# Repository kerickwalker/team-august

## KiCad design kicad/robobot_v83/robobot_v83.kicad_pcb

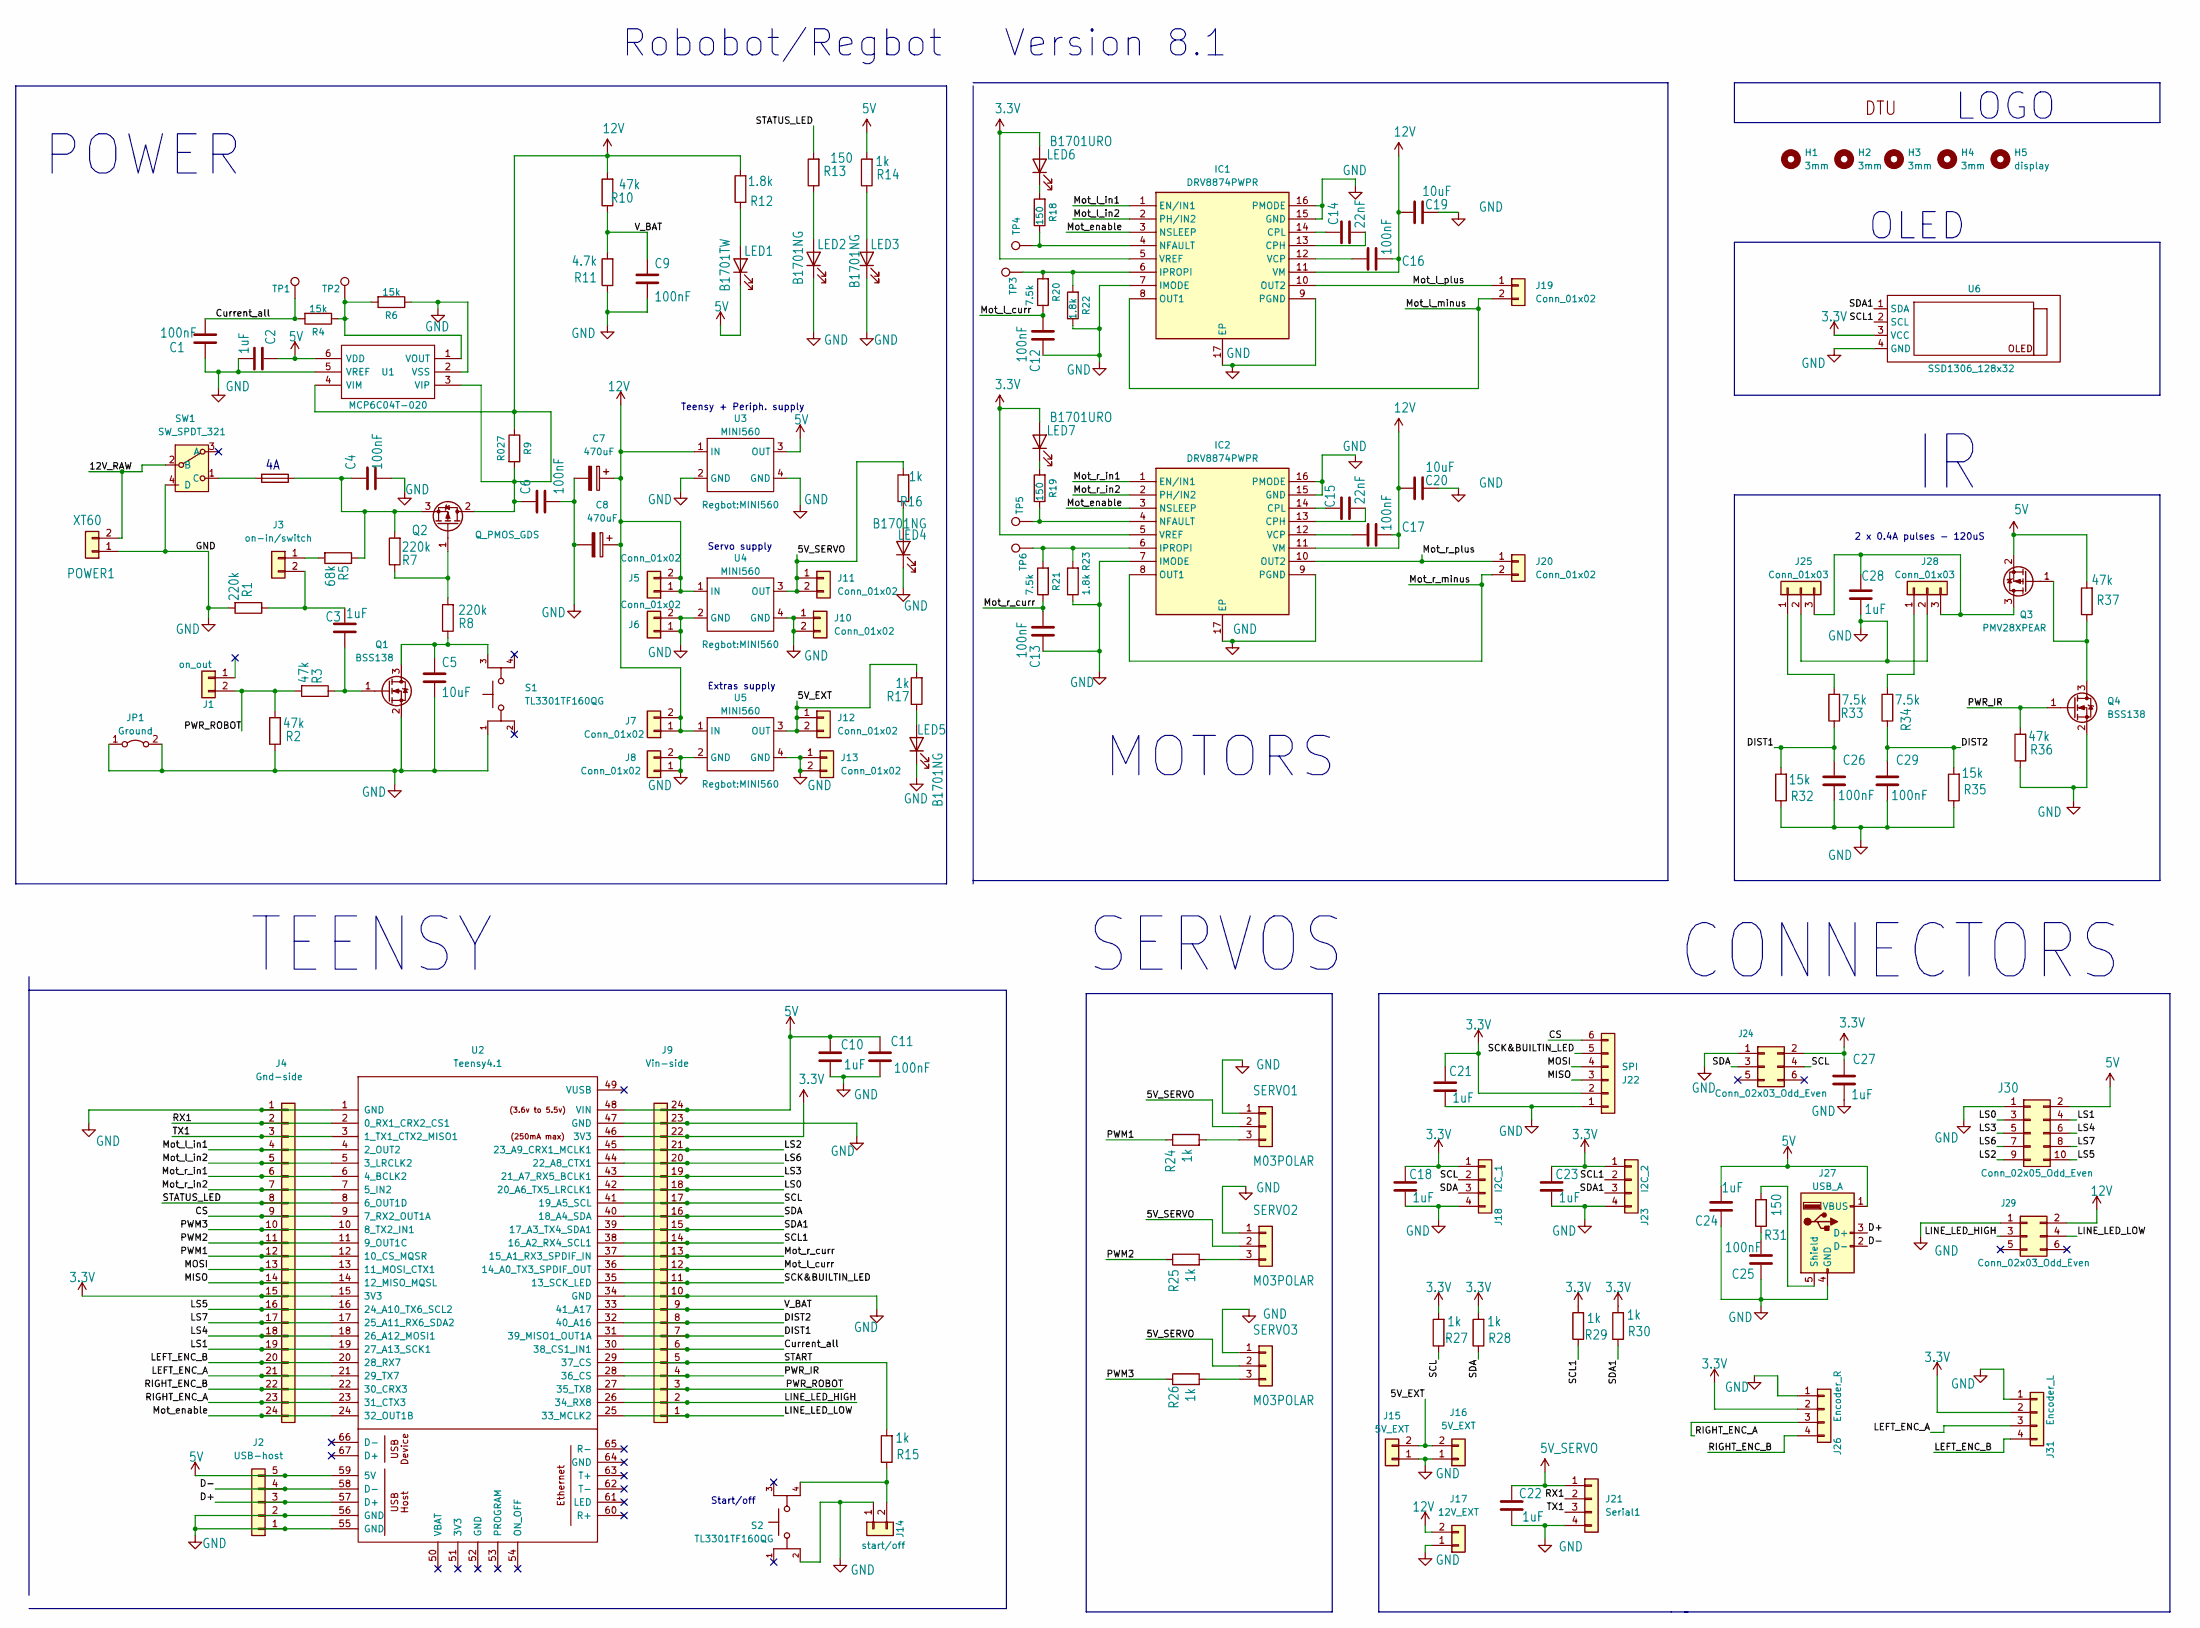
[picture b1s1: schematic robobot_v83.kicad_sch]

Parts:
C1, C4, C6, C9, C11, C12, C13, C16, C17, C25, C26, C29: 100nF; C_0805_2012Metric
C2, C3, C10, C18, C21, C22, C23, C24, C27, C28: 1uF; C_0805_2012Metric
C5, C19, C20: 10uF; C_0805_2012Metric
C7, C8: 470uF; C_Radial_D10.0mm_H16.0mm_P5.00mm
C14, C15: 22nF; C_0805_2012Metric
FUSE1: 4A; Fuseholder_Littelfuse_Nano2_154x
H1, H2, H3, H4: 3mm; MountingHole_3.2mm_M3; Mfg Part # not mounted
H5: display; MountingHole_3.2mm_M3; Mfg Part # not mounted
IC1, IC2: DRV8874PWPR; SOP65P640X120-17N; Mouser Part Number 595-DRV8874PWPR
J1: on_out; JST_PH_B2B-PH-K_1x02_P2.00mm_Vertical
J2: USB-host; PinSocket_1x05_P2.54mm_Vertical
J3: on-in/switch; JST_PH_B2B-PH-K_1x02_P2.00mm_Vertical
J4: Gnd-side; PinSocket_1x24_P2.54mm_Vertical; Mfg Part # not mounted
J5, J7: Conn_01x02; PinSocket_1x02_P2.54mm_Vertical
J6, J8, J10, J11, J12, J13: Conn_01x02; PinHeader_1x02_P2.54mm_Vertical
J9: Vin-side; PinSocket_1x24_P2.54mm_Vertical; Mfg Part # not mounted
J14: start/off; JST_PH_B2B-PH-K_1x02_P2.00mm_Vertical
J15, J16: 5V_EXT; JST_PH_B2B-PH-K_1x02_P2.00mm_Vertical
J17: 12V_EXT; JST_PH_B2B-PH-K_1x02_P2.00mm_Vertical
J18: I2C_1; JST_PH_B4B-PH-K_1x04_P2.00mm_Vertical
J19, J20: Conn_01x02; Molex_KK-254_AE-6410-02A_1x02_P2.54mm_Vertical
J21: Serial1; JST_PH_B4B-PH-K_1x04_P2.00mm_Vertical
J22: SPI; JST_PH_B6B-PH-K_1x06_P2.00mm_Vertical; Mfg Part # not mounted
J23: I2C_2; JST_PH_B4B-PH-K_1x04_P2.00mm_Vertical
J24, J29: Conn_02x03_Odd_Even; IDC-Header_2x03_P2.54mm_Vertical
J25, J28: Conn_01x03; JST_PH_B3B-PH-K_1x03_P2.00mm_Vertical
J26: Encoder_R; JST_PH_B4B-PH-K_1x04_P2.00mm_Vertical
J27: USB_A; USB_A_ASSMANN_A-TOP_VERTICAL
J30: Conn_02x05_Odd_Even; IDC-Header_2x05_P2.54mm_Vertical
J31: Encoder_L; JST_PH_B4B-PH-K_1x04_P2.00mm_Vertical
JP1: Ground; PinHeader_1x02_P2.54mm_Vertical
LED1: B1701TW; LED_0805_2012Metric
LED2, LED3, LED4, LED5: B1701NG; LED_0805_2012Metric
LED6, LED7: B1701URO; LED_0805_2012Metric
POWER1: XT60
Q1, Q4: BSS138; SOT-23
Q2: Q_PMOS_GDS; D-PAK_TO252AA
Q3: PMV28XPEAR; SOT-23
R1, R7, R8: 220k; R_0805_2012Metric
R2, R3, R10, R36, R37: 47k; R_0805_2012Metric
R4, R6, R32, R35: 15k; R_0805_2012Metric
R5: 68k; R_0805_2012Metric
R9: R027; R_1206_3216Metric
R11: 4.7k; R_0805_2012Metric
R12, R22, R23: 1.8k; R_0805_2012Metric
R13, R18, R19, R31: 150; R_0805_2012Metric
R14, R15, R16, R17, R24, R25, R26, R27, R28, R29, R30: 1k; R_0805_2012Metric
R20, R21, R33, R34: 7.5k; R_0805_2012Metric
S1, S2: TL3301TF160QG; TL3301; PARTREV E
SERVO1, SERVO2, SERVO3: M03POLAR; MOLEX-1X3
SW1: SW_SPDT_321; RS-PRO-1MS1T2B3M7QES; Mfg Part # not mounted
TP1, TP2, TP3, TP4, TP5, TP6: sup.cur.; TestPoint_Pad_D1.5mm
U1: MCP6C04T-020; SOT95P280X145-6N; Manufacturer_Part_Number MCP6C04T-020E/CHY; Mouser Part Number 579-MCP6C04T020ECHY
U2: Teensy4.1; Teensy41
U3, U4, U5: MINI560
U6: SSD1306_128x32; PinSocket_1x04_P2.54mm_Vertical
U$1: DTUMEDIUM-9MM; DTU-MEDIUM-9MM

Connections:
+3.3V: C18.1, C21.1, C23.1, C27.1, IC1.5 (VREF), IC2.5 (VREF), J4.15, J9.22, J18.1, J22.2, J23.1, J24.2, J26.2, J31.2, LED6.2 (A), LED7.2 (A), R27.2, R28.2, R29.2, R30.2, U2.15 (3V3), U2.46 (3V3), U6.3 (VCC)
+12V: C6.1, C7.1, C8.1, C16.2, C17.2, C19.1, C20.1, IC1.11 (VM), IC2.11 (VM), J5.1, J5.2, J7.1, J7.2, J17.2, J29.2, Q2.2 (D), R9.1, R9.2, R10.2, R12.2, U1.3 (VIP), U1.4 (VIM), U3.1 (IN), U4.1 (IN), U5.1 (IN)
/5V_EXT: J12.1, J12.2, J15.2, J16.2, R17.2, U5.3 (OUT)
/5V_SERVO: J11.1, J11.2, R16.2, SERVO1.2, SERVO2.2, SERVO3.2, U4.3 (OUT)
/12V_RAW: POWER1.2, SW1.2 (B)
/CS: J4.9, J22.6, U2.9 (7_RX2_OUT1A)
/Current_all: C1.2, J9.6, R4.2, TP1.1, U2.30 (38_CS1_IN1)
/D+: J2.3, J27.3 (D+), U2.57 (D+)
/D-: J2.4, J27.2 (D-), U2.58 (D-)
/DIST1: C26.1, J9.7, R32.2, R33.1, U2.31 (39_MISO1_OUT1A)
/DIST2: C29.1, J9.8, R34.1, R35.2, U2.32 (40_A16)
/LEFT_ENC_A: J4.21, J31.3, U2.21 (29_TX7)
/LEFT_ENC_B: J4.20, J31.4, U2.20 (28_RX7)
/LINE_LED_HIGH: J9.2, J29.3, U2.26 (34_RX8)
/LINE_LED_LOW: J9.1, J29.4, U2.25 (33_MCLK2)
/LS0: J9.18, J30.3, U2.42 (20_A6_TX5_LRCLK1)
/LS1: J4.19, J30.4, U2.19 (27_A13_SCK1)
/LS2: J9.21, J30.9, U2.45 (23_A9_CRX1_MCLK1)
/LS3: J9.19, J30.5, U2.43 (21_A7_RX5_BCLK1)
/LS4: J4.18, J30.6, U2.18 (26_A12_MOSI1)
/LS5: J4.16, J30.10, U2.16 (24_A10_TX6_SCL2)
/LS6: J9.20, J30.7, U2.44 (22_A8_CTX1)
/LS7: J4.17, J30.8, U2.17 (25_A11_RX6_SDA2)
/MISO: J4.14, J22.3, U2.14 (12_MISO_MQSL)
/MOSI: J4.13, J22.4, U2.13 (11_MOSI_CTX1)
/Mot_enable: IC1.3 (NSLEEP), IC2.3 (NSLEEP), J4.24, U2.24 (32_OUT1B)
/Mot_l_curr: C12.2, J9.12, R20.1, U2.36 (14_A0_TX3_SPDIF_OUT)
/Mot_l_in1: IC1.1 (EN/IN1), J4.4, U2.4 (2_OUT2)
/Mot_l_in2: IC1.2 (PH/IN2), J4.5, U2.5 (3_LRCLK2)
/Mot_l_minus: IC1.8 (OUT1), J19.2
/Mot_l_plus: IC1.10 (OUT2), J19.1
/Mot_r_curr: C13.2, J9.13, R21.1, U2.37 (15_A1_RX3_SPDIF_IN)
/Mot_r_in1: IC2.1 (EN/IN1), J4.6, U2.6 (4_BCLK2)
/Mot_r_in2: IC2.2 (PH/IN2), J4.7, U2.7 (5_IN2)
/Mot_r_minus: IC2.8 (OUT1), J20.2
/Mot_r_plus: IC2.10 (OUT2), J20.1
/PWM1: J4.12, R24.1, U2.12 (10_CS_MQSR)
/PWM2: J4.11, R25.1, U2.11 (9_OUT1C)
/PWM3: J4.10, R26.1, U2.10 (8_TX2_IN1)
/PWR_IR: J9.4, Q4.1 (G), R36.2, U2.28 (36_CS)
/PWR_ROBOT: J1.2, J9.3, R2.2, R3.2, U2.27 (35_TX8)
/RIGHT_ENC_A: J4.23, J26.3, U2.23 (31_CTX3)
/RIGHT_ENC_B: J4.22, J26.4, U2.22 (30_CRX3)
/RX1: J4.2, J21.2, U2.2 (0_RX1_CRX2_CS1)
/SCK&BUILTIN_LED: J9.11, J22.5, U2.35 (13_SCK_LED)
/SCL: J9.17, J18.2, J24.4, R27.1, U2.41 (19_A5_SCL)
/SCL1: J9.14, J23.2, R29.1, U2.38 (16_A2_RX4_SCL1), U6.2 (SCL)
/SDA: J9.16, J18.3, J24.3, R28.1, U2.40 (18_A4_SDA)
/SDA1: J9.15, J23.3, R30.1, U2.39 (17_A3_TX4_SDA1), U6.1 (SDA)
/START: J9.5, R15.2, U2.29 (37_CS)
/STATUS_LED: J4.8, R13.2, U2.8 (6_OUT1D)
/TX1: J4.3, J21.3, U2.3 (1_TX1_CTX2_MISO1)
/V_BAT: C9.1, J9.9, R10.1, R11.2, U2.33 (41_A17)
GND: C1.1, C2.2, C4.2, C5.2, C6.2, C7.2, C8.2, C9.2, C10.2, C11.2, C12.1, C13.1, C18.2, C19.2, C20.2, C21.2, C22.2, C23.2, C24.2, C25.2, C26.2, C27.2, C28.2, C29.2, IC1.7 (IMODE), IC1.9 (PGND), IC1.15 (GND), IC1.16 (PMODE), IC1.17 (EP), IC2.7 (IMODE), IC2.9 (PGND), IC2.15 (GND), IC2.16 (PMODE), IC2.17 (EP), J2.1, J2.2, J4.1, J6.1, J6.2, J8.1, J8.2, J9.10, J9.23, J10.1, J10.2, J13.1, J13.2, J14.1, J15.1, J16.1, J17.1, J18.4, J21.4, J22.1, J23.4, J24.1, J25.2, J26.1, J27.4 (GND), J28.2, J29.1, J30.1, J31.1, JP1.1 (A), JP1.2 (B), LED2.1 (K), LED3.1 (K), LED4.1 (K), LED5.1 (K), POWER1.1, Q1.2 (S), Q4.2 (S), R1.2, R2.1, R6.1, R11.1, R22.1, R23.1, R32.1, R35.1, R36.1, S1.1, S2.2, SERVO1.1, SERVO2.1, SERVO3.1, SW1.4 (D), U1.2 (VSS), U1.5 (VREF), U2.1 (GND), U2.34 (GND), U2.47 (GND), U2.55 (GND), U2.56 (GND), U3.2 (GND), U3.4 (GND), U4.2 (GND), U4.4 (GND), U5.2 (GND), U5.4 (GND), U6.4 (GND)
unnamed: C25.1, R31.1
unnamed: C14.2, IC1.13 (CPH)
unnamed: C14.1, IC1.14 (CPL)
unnamed: IC1.6 (IPROPI), R20.2, R22.2, TP3.1
unnamed: IC1.4 (NFAULT), R18.1, TP4.1
unnamed: C16.1, IC1.12 (VCP)
unnamed: C15.2, IC2.13 (CPH)
unnamed: C15.1, IC2.14 (CPL)
unnamed: IC2.6 (IPROPI), R21.2, R23.2, TP6.1
unnamed: IC2.4 (NFAULT), R19.1, TP5.1
unnamed: C17.1, IC2.12 (VCP)
unnamed: J3.1, R5.2
unnamed: C3.2, J3.2, R1.1
unnamed: J14.2, R15.1, S2.4
unnamed: J25.1, R33.2
unnamed: C28.1, J25.3, J28.3, Q3.3 (D)
unnamed: J27.5 (Shield), R31.2
unnamed: J28.1, R34.2
unnamed: LED1.2 (A), R12.1
unnamed: LED2.2 (A), R13.1
unnamed: LED3.2 (A), R14.1
unnamed: LED4.2 (A), R16.1
unnamed: LED5.2 (A), R17.1
unnamed: LED6.1 (K), R18.2
unnamed: LED7.1 (K), R19.2
unnamed: C5.1, Q1.3 (D), R8.1, S1.3
unnamed: C3.1, Q1.1 (G), R3.1
unnamed: Q2.1 (G), R7.1, R8.2
unnamed: C4.1, FUSE1.1, Q2.3 (S), R5.1, R7.2
unnamed: Q3.1 (G), Q4.3 (D), R37.1
unnamed: R24.2, SERVO1.3
unnamed: R25.2, SERVO2.3
unnamed: R26.2, SERVO3.3
unnamed: FUSE1.2, SW1.1 (C)
unnamed: R4.1, R6.2, TP2.1, U1.1 (VOUT)

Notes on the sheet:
Teensy + Periph. supply
TEENSY
2 x 0.4A pulses - 120uS
Start/off
Servo supply
MOTORS
Version 8.1
POWER
SERVOS
Robobot/Regbot
OLED
LOGO
CONNECTORS
Extras supply

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
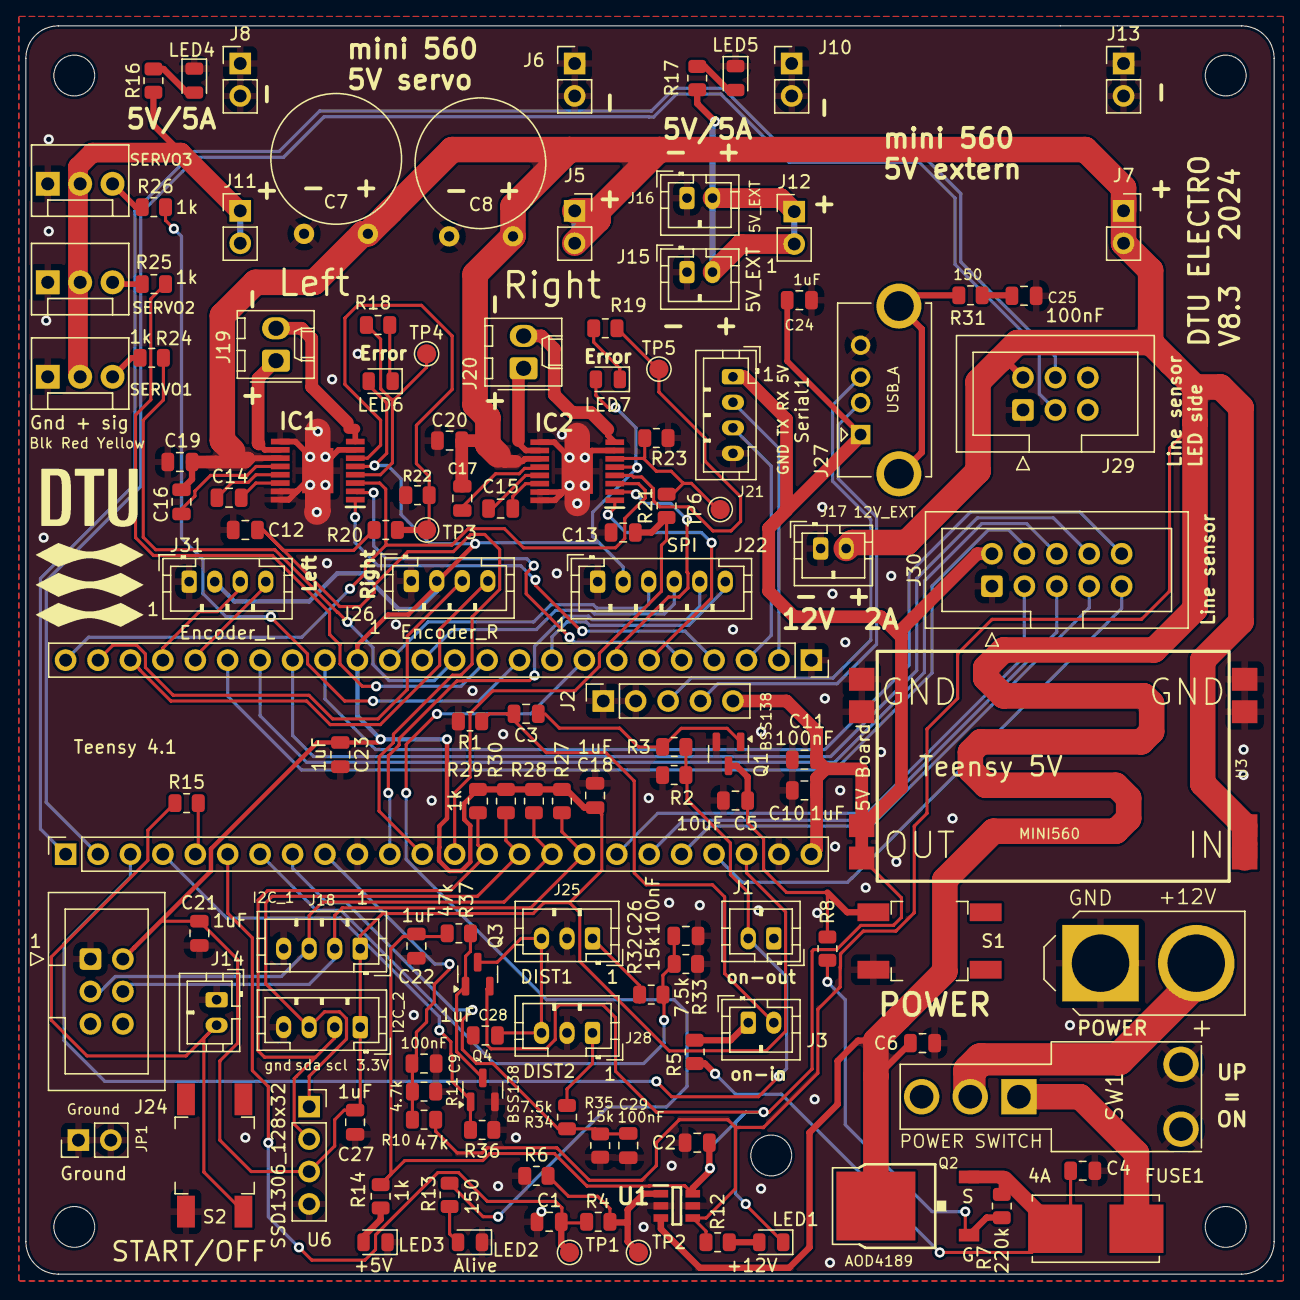
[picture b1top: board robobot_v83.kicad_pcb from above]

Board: 2 copper layers, 97.8 x 97.8 mm, 134 parts (1 on the bottom side), 90 nets.

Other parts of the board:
U$1#2: DTUMEDIUM-9MM; DTU-MEDIUM-9MM

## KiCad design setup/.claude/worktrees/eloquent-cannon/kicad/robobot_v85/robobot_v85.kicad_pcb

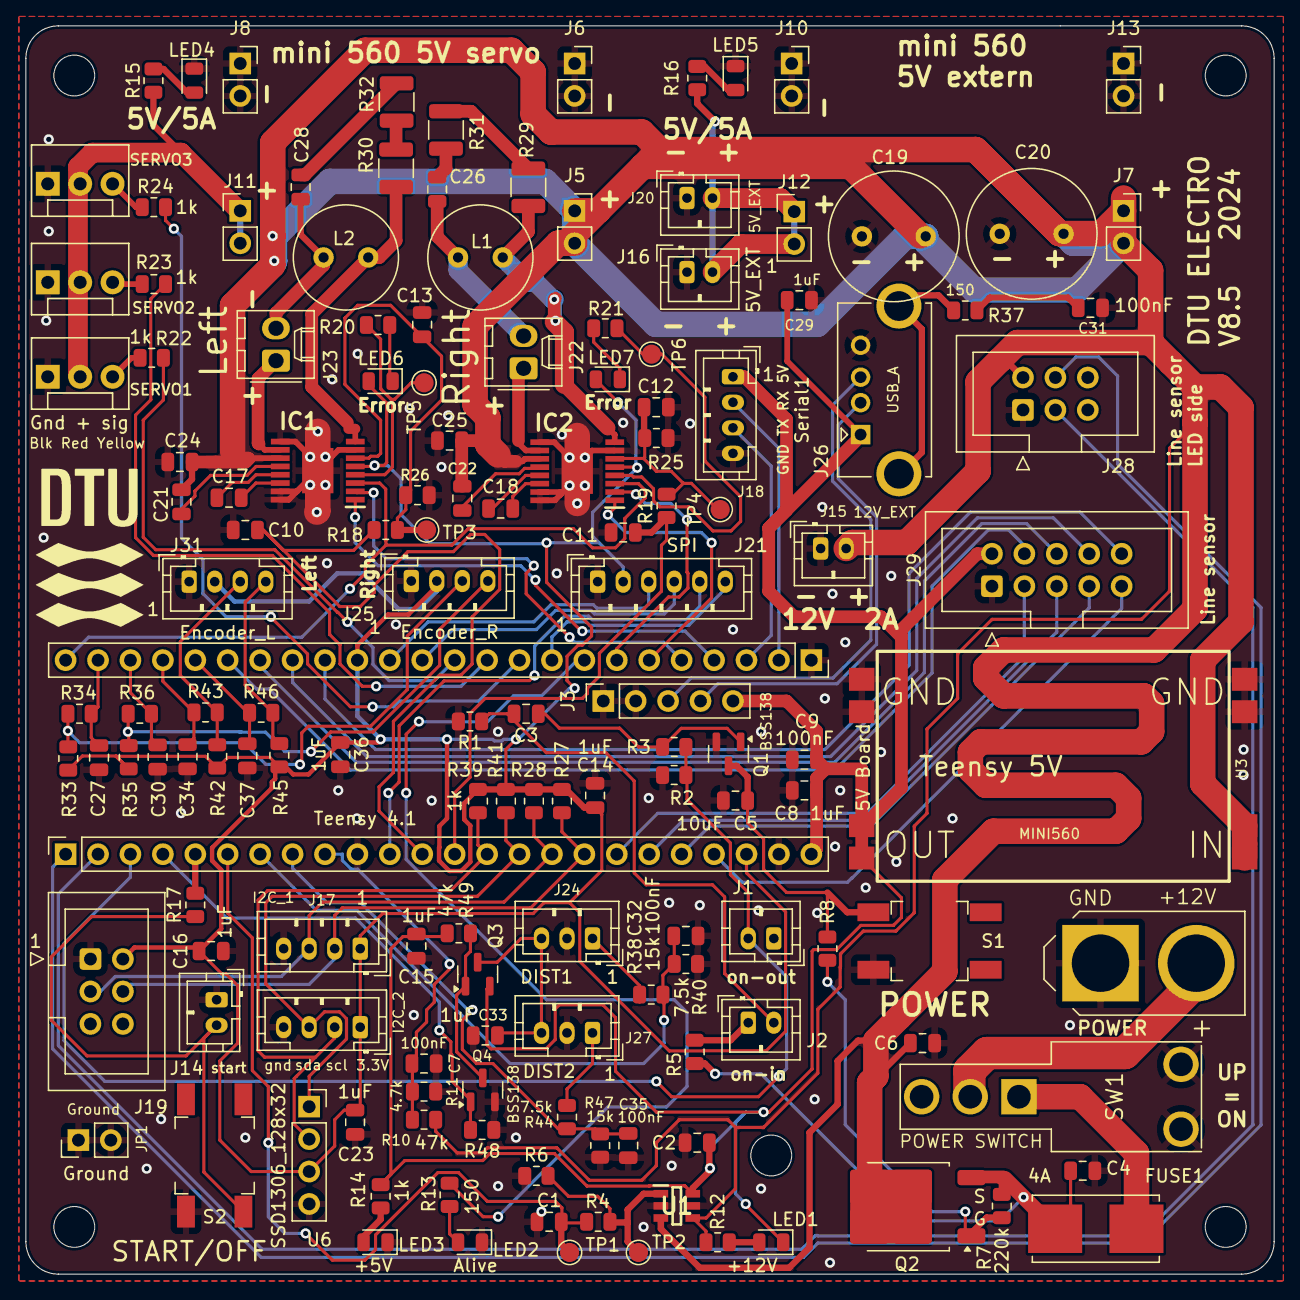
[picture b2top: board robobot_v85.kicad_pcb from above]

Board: 2 copper layers, 97.8 x 97.8 mm, 156 parts (1 on the bottom side), 100 nets.

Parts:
C1, C4, C6, C7, C9, C12, C13, C21, C22, C26, C28, C31, C32, C35: 100nF; C_0805_2012Metric
C2, C3, C8, C14, C15, C16, C23, C29, C33, C36: 1uF; C_0805_2012Metric
C5, C24, C25: 10uF; C_0805_2012Metric
C10, C11, C17, C18: 22nF; C_0805_2012Metric
C19, C20: 470uF; C_Radial_D10.0mm_H16.0mm_P5.00mm
C27, C30, C34, C37: 2.2nF; C_0805_2012Metric
FUSE1: 4A; Fuseholder_Littelfuse_Nano2_154x
H1, H2, H3, H4: 3mm; MountingHole_3.2mm_M3
H5: display; MountingHole_3.2mm_M3
IC1, IC2: DRV8874PWPR; SOP65P640X120-17N
J1: on_out; JST_PH_B2B-PH-K_1x02_P2.00mm_Vertical
J2: on-in/switch; JST_PH_B2B-PH-K_1x02_P2.00mm_Vertical
J3: USB-host; PinSocket_1x05_P2.54mm_Vertical
J4: Gnd-side; PinSocket_1x24_P2.54mm_Vertical
J5, J6, J7, J8, J10, J13: Conn_01x02; PinSocket_1x02_P2.54mm_Vertical
J9: Vin-side; PinSocket_1x24_P2.54mm_Vertical
J11, J12: Conn_01x02; PinHeader_1x02_P2.54mm_Vertical
J14: start/off; JST_PH_B2B-PH-K_1x02_P2.00mm_Vertical
J15: 12V_EXT; JST_PH_B2B-PH-K_1x02_P2.00mm_Vertical
J16, J20: 5V_EXT; JST_PH_B2B-PH-K_1x02_P2.00mm_Vertical
J17: I2C_1; JST_PH_B4B-PH-K_1x04_P2.00mm_Vertical
J18: Serial1; JST_PH_B4B-PH-K_1x04_P2.00mm_Vertical
J19, J28: Conn_02x03_Odd_Even; IDC-Header_2x03_P2.54mm_Vertical
J21: SPI; JST_PH_B6B-PH-K_1x06_P2.00mm_Vertical
J22, J23: Conn_01x02; Molex_KK-254_AE-6410-02A_1x02_P2.54mm_Vertical
J24, J27: Conn_01x03; JST_PH_B3B-PH-K_1x03_P2.00mm_Vertical
J25: Encoder_R; JST_PH_B4B-PH-K_1x04_P2.00mm_Vertical
J26: USB_A; USB_A_ASSMANN_A-TOP_VERTICAL
J29: Conn_02x05_Odd_Even; IDC-Header_2x05_P2.54mm_Vertical
J30: I2C_2; JST_PH_B4B-PH-K_1x04_P2.00mm_Vertical
J31: Encoder_L; JST_PH_B4B-PH-K_1x04_P2.00mm_Vertical
JP1: Ground; PinHeader_1x02_P2.54mm_Vertical
L1, L2: 20uH; C_Radial_D8.0mm_H11.5mm_P3.50mm
LED1: B1701TW; LED_0805_2012Metric
LED2, LED3, LED4, LED5: B1701NG; LED_0805_2012Metric
LED6, LED7: B1701URO; LED_0805_2012Metric
POWER1: XT60
Q1, Q4: BSS138; SOT-23
Q2: Q_PMOS_GDS; TO-252-2
Q3: PMV28XPEAR; SOT-23
R1, R7, R8: 220k; R_0805_2012Metric
R2, R3, R10, R48, R49: 47k; R_0805_2012Metric
R4, R6, R38, R47: 15k; R_0805_2012Metric
R5: 68k; R_0805_2012Metric
R11: 4.7k; R_0805_2012Metric
R12, R25, R26: 1.8k; R_0805_2012Metric
R13, R20, R21, R37: 150; R_0805_2012Metric
R14, R15, R16, R17, R22, R23, R24, R27, R28, R34, R36, R39, R41, R43, R46: 1k; R_0805_2012Metric
R18, R19, R33, R35, R40, R42, R44, R45: 7.5k; R_0805_2012Metric
R29, R30, R31, R32: 56R; R_1210_3225Metric
S1, S2: TL3301TF160QG; TL3301
SERVO1, SERVO2, SERVO3: M03POLAR; MOLEX-1X3
SW1: SW_SPDT_321; RS-PRO-1MS1T2B3M7QES
TP1, TP2, TP3, TP4, TP5, TP6: sup.cur.; TestPoint_Pad_D1.5mm
U1: MCP6C04T-020; SOT95P280X145-6N
U3: MINI560
U6: SSD1306_128x32; PinSocket_1x04_P2.54mm_Vertical
U$1, U$1#2: DTUMEDIUM-9MM; DTU-MEDIUM-9MM

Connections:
+3.3V: C14.1, C16.1, C23.1, C36.1, IC1.5 (VREF), IC2.5 (VREF), J4.15, J9.22, J17.1, J19.2, J21.2, J25.2, J30.1, J31.2, LED6.2 (A), LED7.2 (A), R27.2, R28.2, R33.2, R35.2, R39.2, R41.2, R42.2, R45.2, U6.3 (VCC)
+5V: C2.1, C8.1, C9.1, C15.1, C29.1, J3.5, J9.24, J18.1, J26.1 (VBUS), J29.2, LED1.1 (K), Q3.2 (S), R14.2, R49.2, U1.6 (VDD), U3.3 (OUT)
+12V: C6.1, C19.1, C20.1, C21.2, C22.2, C24.1, C25.1, IC1.11 (VM), IC2.11 (VM), J5.1, J5.2, J7.1, J7.2, J15.2, J28.2, Q2.2 (D), R10.2, R12.2, U1.3 (VIP), U1.4 (VIM), U3.1 (IN)
/5V_EXT: J12.1, J12.2, J16.2, J20.2, R16.2
/5V_SERVO: J11.1, J11.2, R15.2, SERVO1.2, SERVO2.2, SERVO3.2
/12V_RAW: POWER1.2, SW1.2 (B)
/CS: J4.9, J21.6
/Current_all: C1.2, J9.6, R4.2, TP1.1
/D+: J3.3, J26.3 (D+)
/D-: J3.4, J26.2 (D-)
/DIST1: C32.1, J9.7, R38.2, R40.1
/DIST2: C35.1, J9.8, R44.1, R47.2
/LEFT_ENC_A: C34.1, J4.21, R43.1
/LEFT_ENC_B: C37.1, J4.20, R46.1
/LINE_LED_HIGH: J9.2, J28.3
/LINE_LED_LOW: J9.1, J28.4
/LS0: J9.18, J29.3
/LS1: J4.19, J29.4
/LS2: J9.21, J29.9
/LS3: J9.19, J29.5
/LS4: J4.18, J29.6
/LS5: J4.16, J29.10
/LS6: J9.20, J29.7
/LS7: J4.17, J29.8
/MISO: J4.14, J21.3
/MOSI: J4.13, J21.4
/Mot_enable: IC1.3 (NSLEEP), IC2.3 (NSLEEP), J4.24
/Mot_l_curr: C10.2, J9.12, R18.1
/Mot_l_in1: IC1.1 (EN/IN1), J4.4
/Mot_l_in2: IC1.2 (PH/IN2), J4.5
/Mot_l_minus: C28.2, J23.2, L2.2
/Mot_l_plus: IC1.10 (OUT2), J23.1
/Mot_r_curr: C11.2, J9.13, R19.1
/Mot_r_in1: IC2.1 (EN/IN1), J4.6
/Mot_r_in2: IC2.2 (PH/IN2), J4.7
/Mot_r_minus: C26.2, J22.2, L1.2
/Mot_r_plus: IC2.10 (OUT2), J22.1
/PWM1: J4.12, R22.1
/PWM2: J4.11, R23.1
/PWM3: J4.10, R24.1
/PWR_IR: J9.4, Q4.1 (G), R48.2
/PWR_ROBOT: J1.2, J9.3, R2.2, R3.2
/RIGHT_ENC_A: C27.1, J4.23, R34.1
/RIGHT_ENC_B: C30.1, J4.22, R36.1
/RX1: J4.2, J18.2
/SCK&BUILTIN_LED: J9.11, J21.5
/SCL: J9.17, J17.2, J19.4, R27.1
/SCL1: J9.14, J30.2, R39.1, U6.2 (SCL)
/SDA: J9.16, J17.3, J19.3, R28.1
/SDA1: J9.15, J30.3, R41.1, U6.1 (SDA)
/START: J9.5, R17.2
/STATUS_LED: J4.8, R13.2
/TX1: J4.3, J18.3
/V_BAT: C7.1, J9.9, R10.1, R11.2
GND: C1.1, C2.2, C4.2, C5.2, C6.2, C7.2, C8.2, C9.2, C10.1, C11.1, C12.1, C13.1, C14.2, C15.2, C16.2, C19.2, C20.2, C23.2, C24.2, C25.2, C27.2, C29.2, C30.2, C31.2, C32.2, C33.2, C34.2, C35.2, C36.2, C37.2, IC1.7 (IMODE), IC1.9 (PGND), IC1.15 (GND), IC1.16 (PMODE), IC1.17 (EP), IC2.7 (IMODE), IC2.9 (PGND), IC2.15 (GND), IC2.16 (PMODE), IC2.17 (EP), J3.1, J3.2, J4.1, J6.1, J6.2, J8.1, J8.2, J9.10, J9.23, J10.1, J10.2, J13.1, J13.2, J14.1, J15.1, J16.1, J17.4, J18.4, J19.1, J20.1, J21.1, J24.2, J25.1, J26.4 (GND), J27.2, J28.1, J29.1, J30.4, J31.1, JP1.1 (A), JP1.2 (B), LED2.1 (K), LED3.1 (K), LED4.1 (K), LED5.1 (K), POWER1.1, Q1.2 (S), Q4.2 (S), R1.2, R2.1, R6.1, R11.1, R25.1, R26.1, R38.1, R47.1, R48.1, S1.1, S2.2, SERVO1.1, SERVO2.1, SERVO3.1, SW1.4 (D), U1.2 (VSS), U1.5 (VREF), U3.2 (GND), U3.4 (GND), U6.4 (GND)
unnamed: C26.1, R31.1
unnamed: C28.1, R32.1
unnamed: C31.1, R37.1
unnamed: C17.2, IC1.13 (CPH)
unnamed: C17.1, IC1.14 (CPL)
unnamed: C13.2, IC1.6 (IPROPI), R18.2, R26.2, TP3.1
unnamed: IC1.4 (NFAULT), R20.1, TP5.1
unnamed: IC1.8 (OUT1), L2.1, R30.2
unnamed: C21.1, IC1.12 (VCP)
unnamed: C18.2, IC2.13 (CPH)
unnamed: C18.1, IC2.14 (CPL)
unnamed: C12.2, IC2.6 (IPROPI), R19.2, R25.2, TP4.1
unnamed: IC2.4 (NFAULT), R21.1, TP6.1
unnamed: IC2.8 (OUT1), L1.1, R29.2
unnamed: C22.1, IC2.12 (VCP)
unnamed: J2.1, R5.2
unnamed: C3.2, J2.2, R1.1
unnamed: J14.2, R17.1, S2.4
unnamed: J24.1, R40.2
unnamed: C33.1, J24.3, J27.3, Q3.3 (D)
unnamed: J25.3, R33.1, R34.2
unnamed: J25.4, R35.1, R36.2
unnamed: J26.5 (Shield), R37.2
unnamed: J27.1, R44.2
unnamed: J31.3, R42.1, R43.2
unnamed: J31.4, R45.1, R46.2
unnamed: LED1.2 (A), R12.1
unnamed: LED2.2 (A), R13.1
unnamed: LED3.2 (A), R14.1
unnamed: LED4.2 (A), R15.1
unnamed: LED5.2 (A), R16.1
unnamed: LED6.1 (K), R20.2
unnamed: LED7.1 (K), R21.2
unnamed: C5.1, Q1.3 (D), R8.1, S1.3
unnamed: C3.1, Q1.1 (G), R3.1
unnamed: Q2.1 (G), R7.1, R8.2
unnamed: C4.1, FUSE1.1, Q2.3 (S), R5.1, R7.2
unnamed: Q3.1 (G), Q4.3 (D), R49.1
unnamed: R29.1, R31.2
unnamed: R30.1, R32.2
unnamed: R22.2, SERVO1.3
unnamed: R23.2, SERVO2.3
unnamed: R24.2, SERVO3.3
unnamed: FUSE1.2, SW1.1 (C)
unnamed: R4.1, R6.2, TP2.1, U1.1 (VOUT)

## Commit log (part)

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2026-03-02 add python script for teleop control
2026-03-02 calibrate hsv values
2026-03-06 remove accidentally added copyright
2026-03-06 code cleanup
2026-03-08 Kalman filter implementation in separate files.
2026-03-08 fix in the model related to pitch
2026-03-08 Multi sensor implementation of Kalman filter.
2026-03-08 updated folder strucutre and made changes accordingly
2026-03-08 Sensor conversion has been created that will map raw sensor to states
2026-03-08 Final implementation using the raw sensor input for the Kalman filter with the converter.
2026-03-09 camera calibration scripts and params
2026-03-09 Add perception module: line detection, ground projection, and ArUco detection
2026-03-11 Clean baseline: full source snapshot
2026-03-11 Robot current state: teensy-dev starting point
2026-03-11 full system re-verification after git revert, all fixes confirmed working
2026-03-12 Track build outputs and sync all changes: add build artifacts, update logs, and code changes for line following, calibration, and debug.
2026-03-12 Add notes bundle, rolling line calibration, --test flag, and master-lost stop
2026-03-12 reverted mqtt-client and sedge changes
2026-03-13 implemented PID, sedge: tuning block at top, with print options
2026-03-13 line-follow: recovery turn toward lastLineSide, recovery_timeout_s in sedge, doc in notes
2026-03-13 update on params
2026-03-13 Kalman real-time application for the robot.
2026-03-13 kalman is back
2026-03-13 added a ball catching test function
2026-03-13 added functionality to control the robot and servo manually
2026-03-15 Line follow: crossing-count state machine, leave delay, hard turns at 3+/5+, 4th stop+turn+1.3m, driveTurn/driveDistance, single-line print (crossingCnt, left/rightMost), green/red GPIO, sedge sensor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
2026-03-16 Added more sensors that will be needed.
2026-03-18 Backing up today to save before Friday.
2026-03-18 Kalman filter implementation for teleoperation control
2026-03-18 Internal Kalman class added for fallback
2026-03-18 Added is.quiet under uservice.py
2026-03-18 same
2026-03-18 bug fix 4818923589
2026-03-18 patch
2026-03-18 pushback
2026-03-19 green button, red button and teensy_interfac is handled properly, no master mismatches and no zombie mqtt processes
2026-03-19 standardize teensy_interface process, implement roundabout-test
2026-03-19 rebuilt ip_disp, roundabout tests
2026-03-20 add ball detection functionality with configurable parameters and GUI controls
2026-03-27 Resolve merge conflict in uservice.py, keep upstream version
2026-04-07 initial pure pursuit controller
2026-04-07 ingore CLAUDE.md
2026-04-07 add mqtt_python/CLAUDE.md to .gitignore
2026-04-07 restored notes
2026-04-07 remove unused get-pose.py script and update related documentation
2026-04-07 add debug mode to mqtt_client_path_follow.py for Kalman pose verification
2026-04-07 changed readme
2026-04-10 added roundabout test
2026-04-10 Enhance quiet mode functionality in UService: include debug flag and improve message handling
2026-04-10 refactor: field map, localization, and visualization modules
2026-04-10 Add velocity and turnrate tracking to path-following service
2026-04-10 Refactor code structure for improved readability and maintainability
2026-04-10 Negate trajectory y and heading in drivePathFollow for consistent frame of reference
2026-04-10 Add velocity parameter to compute_command for enhanced control in Pure Pursuit
2026-04-10 Update LOOKAHEAD_DIST and MAX_TURNRATE for improved trajectory tracking
2026-04-10 Refactor SKalman to capture yaw offsets at reset for improved measurement accuracy; update trajectory data and increase LOOKAHEAD_DIST for better tracking.
2026-04-10 Update .gitignore and change log for Pure Pursuit coordinate convention and silent mode enhancements
2026-04-11 Enhance teleoperation script with countdown before start and improve output clarity
2026-04-11 Add interpolate_waypoints.py for cubic-spline resampling of teleop waypoints
2026-04-11 Update path_following.md to document trajectory authoring workflow and clarify waypoint capture process
2026-04-11 Refactor cubic spline implementation in interpolate_waypoints.py to use numpy only, removing scipy dependency; update path_following.md to reflect this change.
2026-04-11 Add plot_trajectory.py for visualizing trajectory data from CSV files
2026-04-13 Update trajectory.csv with new waypoint data for improved path accuracy
2026-04-13 Add roundabout mission architecture and tuning guide
2026-04-14 Adjust roundabout circle diameter to 0.8 meters
2026-04-14 Enhance line-following mission with junction nudge and roundabout functionality
2026-04-14 Refactor line-following mission: streamline crossing logic and remove roundabout handling
    - Simplified mission overview and removed unnecessary comments.
    - Consolidated crossing detection and response logic.
    - Removed roundabout-related code and state management.
    - Updated drive functions to enhance clarity and maintainability.
2026-04-14 Add full mission architecture and tuning guide documentation
    - Introduced comprehensive documentation for the full mission script located in `mqtt_python/mqtt-full-mission.py`.
    - Detailed mission overview, crossing-count mapping, code structure, state machine, and tuning workflow.
    - Included examples for adjusting parameters and running the script.
    - Clarified relationships to other scripts for better understanding of the system architecture.
2026-04-17 Update vision modules
2026-04-18 changes speed to 0.3
2026-04-20 Add gate1 entry tests and sgate_1 implementation updates.
    Made-with: Cursor
2026-04-20 Add new gate entry driving test with turn-in-place alignment
2026-04-20 Add gate detection and approach script using uservice/uteensy framework
2026-04-20 Refactor driveGateApproach logging for clarity and consistency in quiet mode
2026-04-22 kalman fixed
2026-04-24 videos
2026-04-24 Enhance line-following control with approach speed and PID parameter sets for improved roundabout navigation
2026-04-24 Refactor roundabout gate-alignment test to enhance line-following with crossing detection and implement live camera streaming
2026-04-24 Add MQTT teleop control script for Robobot
    - Implement keyboard teleoperation control over MQTT.
    - Support for movement commands: forward, backward, turn left/right, and stop.
    - Include functionality to adjust linear speed and turn rate.
    - Integrate MJPEG web streaming with gate detection overlay.
    - Provide command-line options for silent mode.
    - Handle keypress events with a timeout for smooth control.
2026-04-24 Reorganize mqtt_python mission scripts
2026-04-24 Fix teensy interface path lookup
2026-04-24 Reorganize mqtt_python runtime files
2026-04-24 Add initial configuration file for MQTT robot setup
    - Created `robot.ini` to define service, MQTT, Teensy, encoder, IMU, motor, and joystick settings.
    - Configured logging options and device parameters for various components.
    - Established parameters for velocity, mixer, and GPIO settings to facilitate robot control.
2026-04-25 something
2026-04-27 as left
2026-04-28 pushed to change branch, undo if needed
2026-04-28 kp 0.6, kd 0.1
2026-04-28 adjust PID
2026-04-28 changes to end and pid tuning
2026-04-28 slam trial cleaned
2026-04-29 Add ball collection module and associated test scripts
    - Implemented SCollect class for ball collection with state machine logic in scollect.py.
    - Created test_collect.py for standalone testing of the ball collection module with adjustable parameters.
    - Developed test_servo.py for smoke testing the arm servo, mirroring the behavior in scollect.py.
2026-04-29 Stabilize line PID near sensor edge
2026-04-29 Log minimum turn rescue state
2026-04-29 Guard line steering against derivative jitter
2026-04-29 Soften line following for corners
2026-04-29 push
2026-04-29 Simplify line follower to P-only control
2026-04-29 Add platform ball-to-hole, seesaw-golf, aruco-test tasks; tweak aruco_dock and ramp_to_bowl_line
2026-04-29 Add straight-line recovery before spin
2026-04-29 Add slow settle after line reacquire
2026-04-29 Guard line follower derivative kick
2026-04-30 Use requested profile on line-follow start
2026-04-30 Add forward step to line recovery
2026-04-30 Debounce line loss before recovery
2026-04-30 Use pattern table for line center
2026-04-30 Classify crossings by sensor pattern
2026-04-30 Add sensor pattern diagnostics
2026-04-30 tuning
2026-04-30 Tune line min turn and trim diagnostics
2026-04-30 Add bounded derivative line tuning
2026-04-30 Log PID test output
2026-04-30 Tune line follower minimum turn
2026-04-30 PID log
2026-04-30 improvements to the golf ball collection and deposit system
2026-04-30 Add P-only line follower baseline
2026-04-30 Stop tracking generated log files
2026-04-30 Add servo 3 test mode to test_servo.
    This keeps servo validation focused by allowing a dedicated servo 3 cycle with configurable endpoints, dwell, and speed, without moving servos 1/2.
    Made-with: Cursor
2026-04-30 servo tests
2026-04-30 reformat
2026-04-30 Handle full-line trigger in line follow
2026-04-30 no progress
2026-04-30 Add line edge guard mode
2026-04-30 Update servo smoke test flags
2026-04-30 Add individual servo calibration flags
2026-04-30 Add one-shot servo calibration command
2026-05-01 Set calibrated servo limits
2026-05-01 Clean final mission controller baseline
2026-05-01 servo limits
2026-05-01 Make teleop optional-dependency safe
2026-05-01 Restore test teleop handoff logging
2026-05-01 Restore analog line centering
2026-05-01 Timestamp PID test logs
2026-05-01 Redirect test output to PID log
2026-05-01 tuned
2026-05-01 Add half mission submission
2026-05-01 Add odometry test sequence
2026-05-01 Start half mission after roundabout
2026-05-01 Log line sensor receive gaps
2026-05-01 Use receive age for line stale control
2026-05-01 Simplify line age logging
2026-05-06 Add path following system documentation and academic report prompt
    - Introduced a comprehensive documentation file for the path-following subsystem of the Robobot.
    - Included detailed descriptions of the system overview, data flow, trajectory authoring workflow, Pure Pursuit algorithm, and key parameters.
    - Provided a structured LLM prompt for generating an academic report section on the path-following implementation.
2026-05-06 commands_and_workflow
2026-05-11 Refactor coordinate conventions in waypoint capture and interpolation scripts for consistency with Kalman frame
2026-05-12 Reduce path-following velocity from 0.3 m/s to 0.2 m/s for improved control
2026-05-12 Add MQTT topic logger script and log file
    - Introduced mqtt_topic_logger.py to log selected MQTT topics to console and a JSONL file.
    - Default topics include "robobot/kalman/state" and "robobot/drive/T0/pose".
    - Implemented message handling, logging, and graceful shutdown.
    - Created bismillah.jsonl log file for storing received messages.
    - Updated shutdown.now binary file.
2026-05-12 Add optional live plotting for trajectory visualization during path following
2026-05-12 Refactor live plotting to save trajectory visualization as PNG on exit
2026-05-12 Adjust trajectory coordinate conventions to align with Kalman frame
2026-05-12 Fix trajectory plotting and update comments for Kalman frame alignment
